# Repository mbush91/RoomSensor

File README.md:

# Room Sensor

## TODO

### Updates for JLC Economy

- Temp/Humidity sensor -> AHT20-F
- ACC -> MMA8452QR1
- BLE Module -> nRF52833-QDAA-R + balun and antenna

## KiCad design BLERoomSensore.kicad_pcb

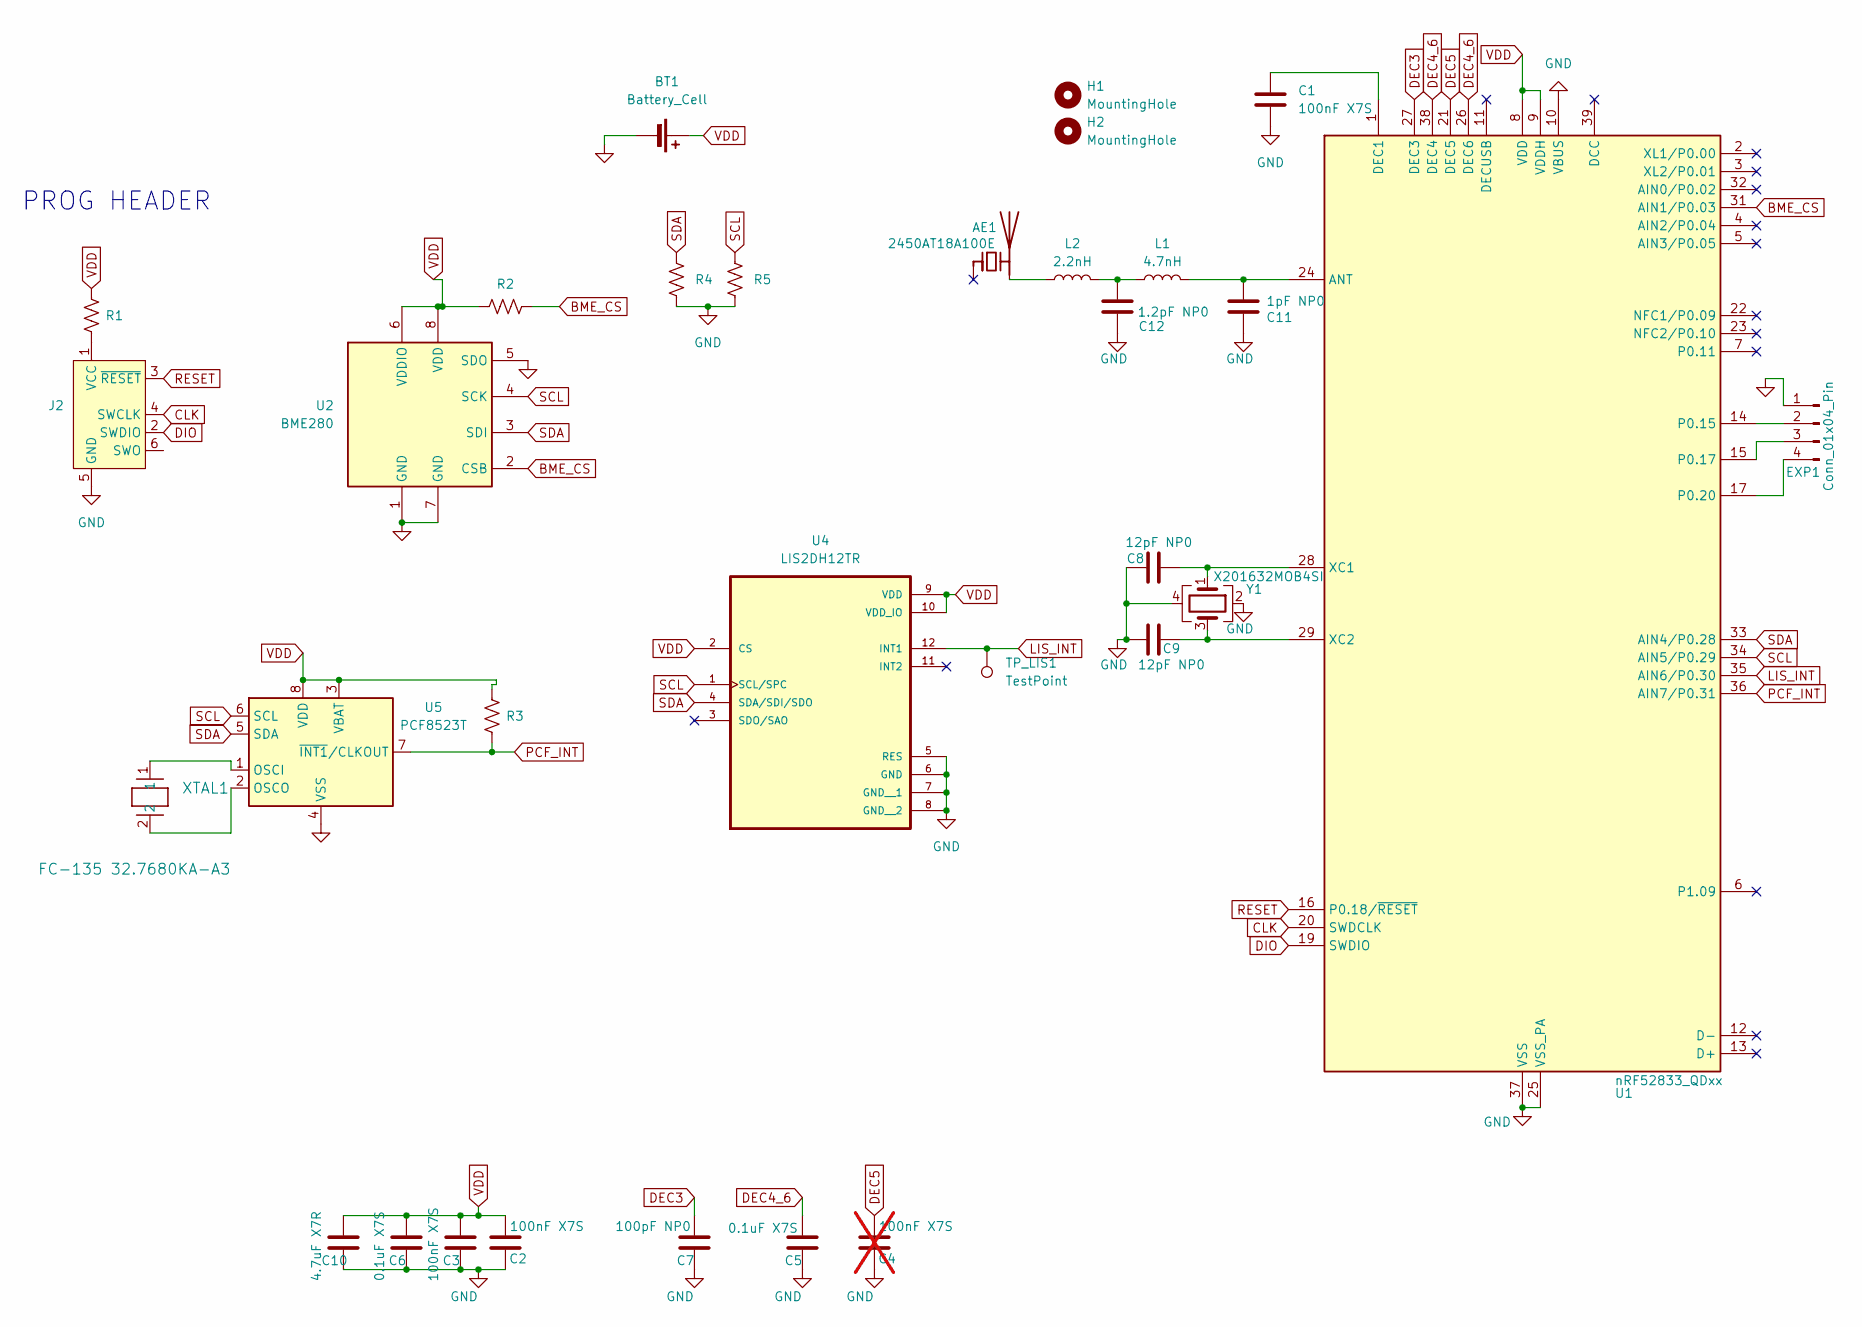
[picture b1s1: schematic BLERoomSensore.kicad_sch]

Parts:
AE1: 2450AT18A100E; C_0603_1608Metric; MPN 2450AT18A100E
BT1: Battery_Cell; BAT_BAT-HLD-003-SMT_MOD; MPN MY-2032-05
C1, C2, C3: 100nF X7S; C_0402_1005Metric_Pad0.74x0.62mm_HandSolder
C4: 100nF X7S; C_0402_1005Metric_Pad0.74x0.62mm_HandSolder; not fitted
C5, C6: 0.1uF X7S; C_0402_1005Metric_Pad0.74x0.62mm_HandSolder
C7: 100pF NP0; C_0402_1005Metric_Pad0.74x0.62mm_HandSolder
C8, C9: 12pF NP0; C_0402_1005Metric_Pad0.74x0.62mm_HandSolder
C10: 4.7uF X7R; C_0603_1608Metric_Pad1.08x0.95mm_HandSolder
C11: 1pF NP0; C_0402_1005Metric_Pad0.74x0.62mm_HandSolder
C12: 1.2pF NP0; C_0402_1005Metric_Pad0.74x0.62mm_HandSolder
EXP1: Conn_01x04_Pin; PinHeader_1x04_P1.27mm_Vertical
H1, H2: MountingHole; MountingHole_2.5mm
J2: Conn_ARM_SWD_TagConnect_TC2030-NL; Tag-Connect_TC2030-IDC-NL_2x03_P1.27mm_Vertical
L1: 4.7nH; L_0402_1005Metric
L2: 2.2nH; L_0402_1005Metric
R1: 0; R_0402_1005Metric_Pad0.72x0.64mm_HandSolder; MPN RC0402JR-070RL
R2, R3: 100k; R_0402_1005Metric_Pad0.72x0.64mm_HandSolder; MPN RC0402FR-07100KL
R4, R5: 10k; R_0402_1005Metric_Pad0.72x0.64mm_HandSolder; MPN RC0402JR-0710KL
TP_LIS1: TestPoint; TestPoint_Pad_D1.0mm
U1: nRF52833_QDxx; QFN-40-1EP_5x5mm_P0.4mm_EP3.6x3.6mm
U2: BME280; Bosch_LGA-8_2.5x2.5mm_P0.65mm_ClockwisePinNumbering; MPN BME280
U4: LIS2DH12TR; PQFN50P200X200100-12N; MPN LIS2DH12TR
U5: PCF8523T; SOIC-8_3.9x4.9mm_P1.27mm; MPN PCF8523T/1,118
XTAL1: FC-135 32.7680KA-A3; XTAL_FC-135R_EPS; MPN FC-12M 32.7680KA-A3
Y1: X201632MOB4SI; Crystal_SMD_2016-4Pin_2.0x1.6mm; MPN X201632MOB4SI

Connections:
BME_CS: R2.2, U1.31 (AIN1/P0.03), U2.2 (CSB)
CLK: J2.4 (SWCLK), U1.20 (SWDCLK)
DEC3: C7.2, U1.27 (DEC3)
DEC4_6: C5.2, U1.26 (DEC6), U1.38 (DEC4)
DEC5: C4.2, U1.21 (DEC5)
DIO: J2.2 (SWDIO), U1.19 (SWDIO)
GND: BT1.2 (-), C1.2, C2.1, C3.1, C4.1, C5.1, C6.1, C7.1, C8.1, C9.2, C10.1, C11.1, C12.1, EXP1.1, J2.5 (GND), R4.1, R5.1, U1.10 (VBUS), U1.25 (VSS_PA), U1.37 (VSS), U1.41 (VSS), U2.1 (GND), U2.5 (SDO), U2.7 (GND), U4.5 (RES), U4.6 (GND), U4.7 (GND__1), U4.8 (GND__2), U5.4 (VSS), Y1.2, Y1.4
LIS_INT: TP_LIS1.1, U1.35 (AIN6/P0.30), U4.12 (INT1)
unnamed: AE1.2 (PCB_Trace), L2.1
unnamed: C12.2, L1.1, L2.2
unnamed: EXP1.2, U1.14 (P0.15)
unnamed: EXP1.3, U1.15 (P0.17)
unnamed: EXP1.4, U1.17 (P0.20)
unnamed: J2.1 (VCC), R1.1
unnamed: C11.2, L1.2, U1.24 (ANT)
unnamed: C1.1, U1.1 (DEC1)
unnamed: C8.2, U1.28 (XC1), Y1.1
unnamed: C9.1, U1.29 (XC2), Y1.3
unnamed: U5.1 (OSCI), XTAL1.1
unnamed: U5.2 (OSCO), XTAL1.2
PCF_INT: R3.1, U1.36 (AIN7/P0.31), U5.7 (~INT1/CLKOUT)
RESET: J2.3 (~RESET), U1.16 (P0.18/~RESET)
SCL: R5.2, U1.34 (AIN5/P0.29), U2.4 (SCK), U4.1 (SCL/SPC), U5.6 (SCL)
SDA: R4.2, U1.33 (AIN4/P0.28), U2.3 (SDI), U4.4 (SDA/SDI/SDO), U5.5 (SDA)
VDD: BT1.1 (+), C2.2, C3.2, C6.2, C10.2, R1.2, R2.1, R3.2, U1.8 (VDD), U1.9 (VDDH), U1.18 (VDD), U1.30 (VDD), U1.40 (VDD), U2.6 (VDDIO), U2.8 (VDD), U4.2 (CS), U4.9 (VDD), U4.10 (VDD_IO), U5.3 (VBAT), U5.8 (VDD)

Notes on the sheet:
PROG HEADER

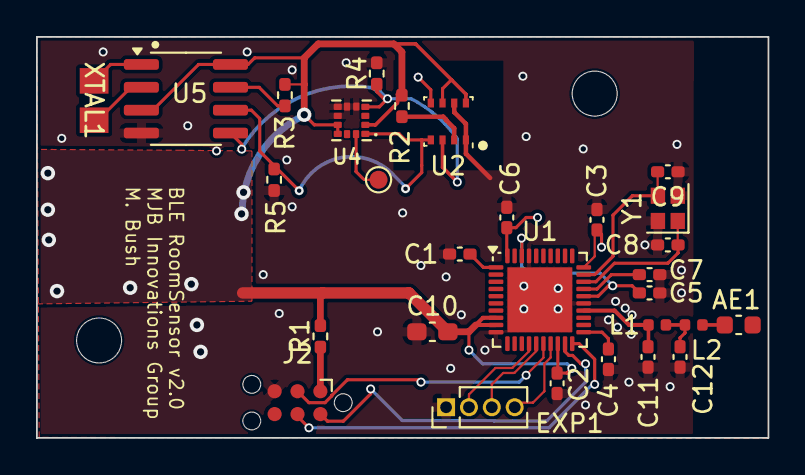
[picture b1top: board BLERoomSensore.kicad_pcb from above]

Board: 2 copper layers, 40.6 x 22.3 mm, 32 parts (1 on the bottom side), 25 nets.

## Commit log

2024-06-12 add gerbers
2025-02-09 Updated sch with ACC and RTK
2025-02-11 Routing Done, no DRC errors
2025-02-11 Add expansion header
2025-02-11 Bunch o production files
2025-02-12 Working on comp changes
